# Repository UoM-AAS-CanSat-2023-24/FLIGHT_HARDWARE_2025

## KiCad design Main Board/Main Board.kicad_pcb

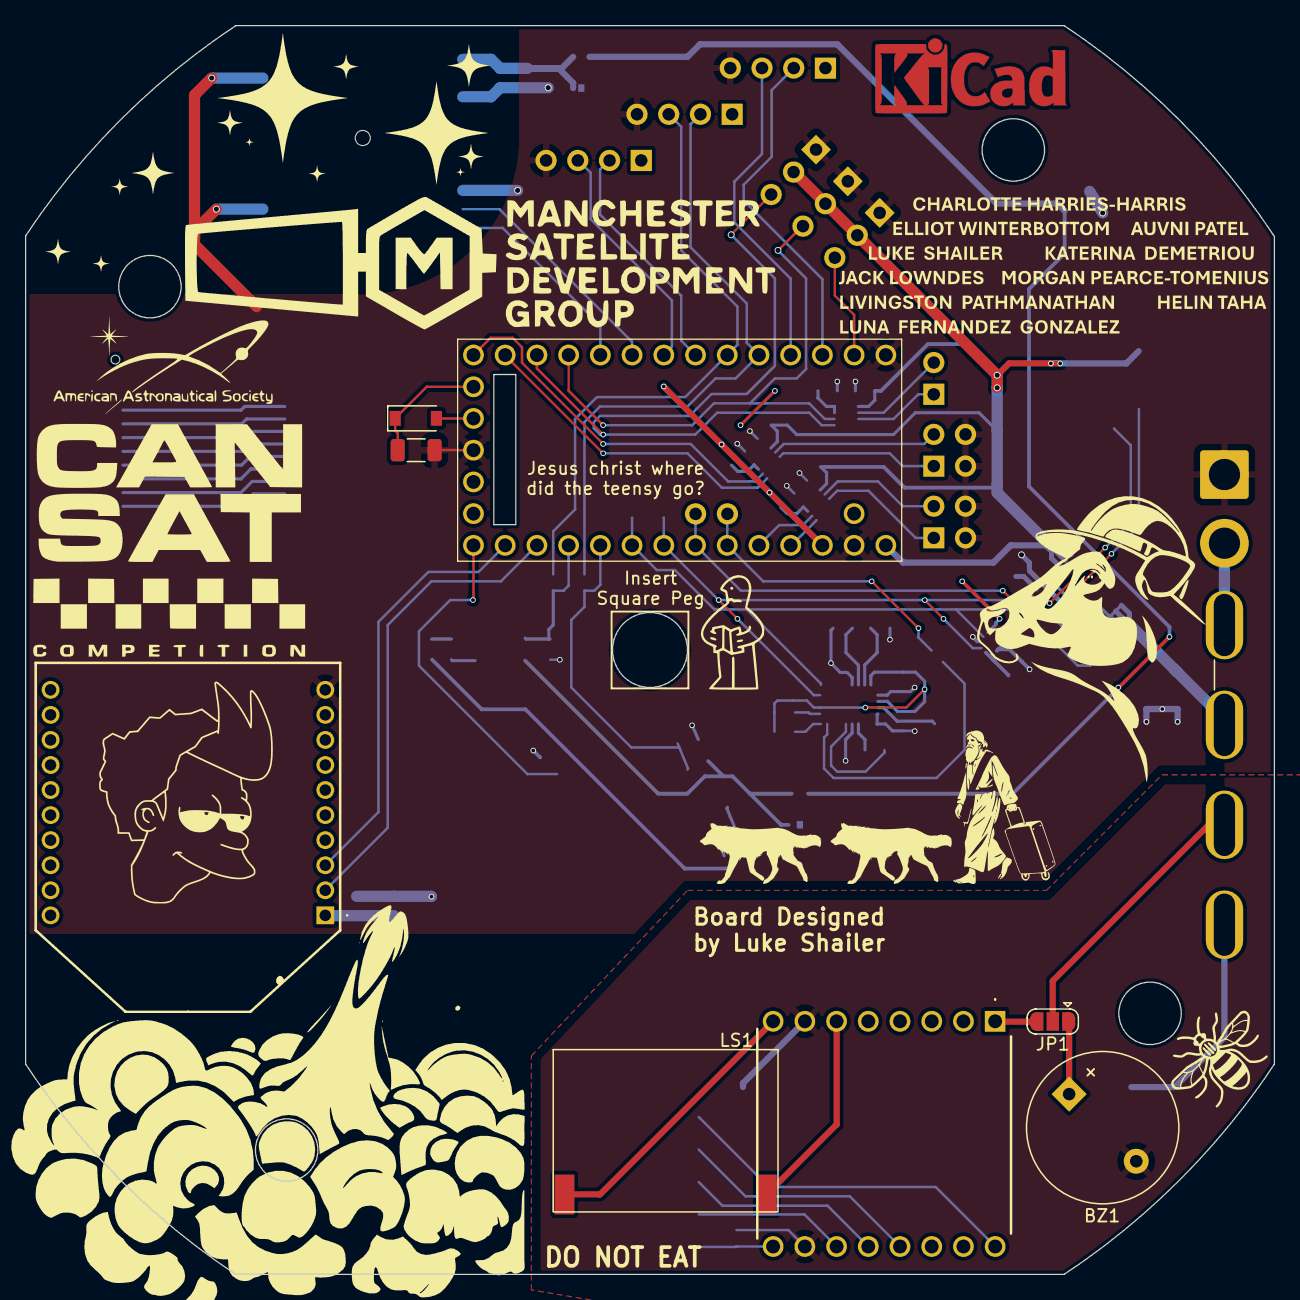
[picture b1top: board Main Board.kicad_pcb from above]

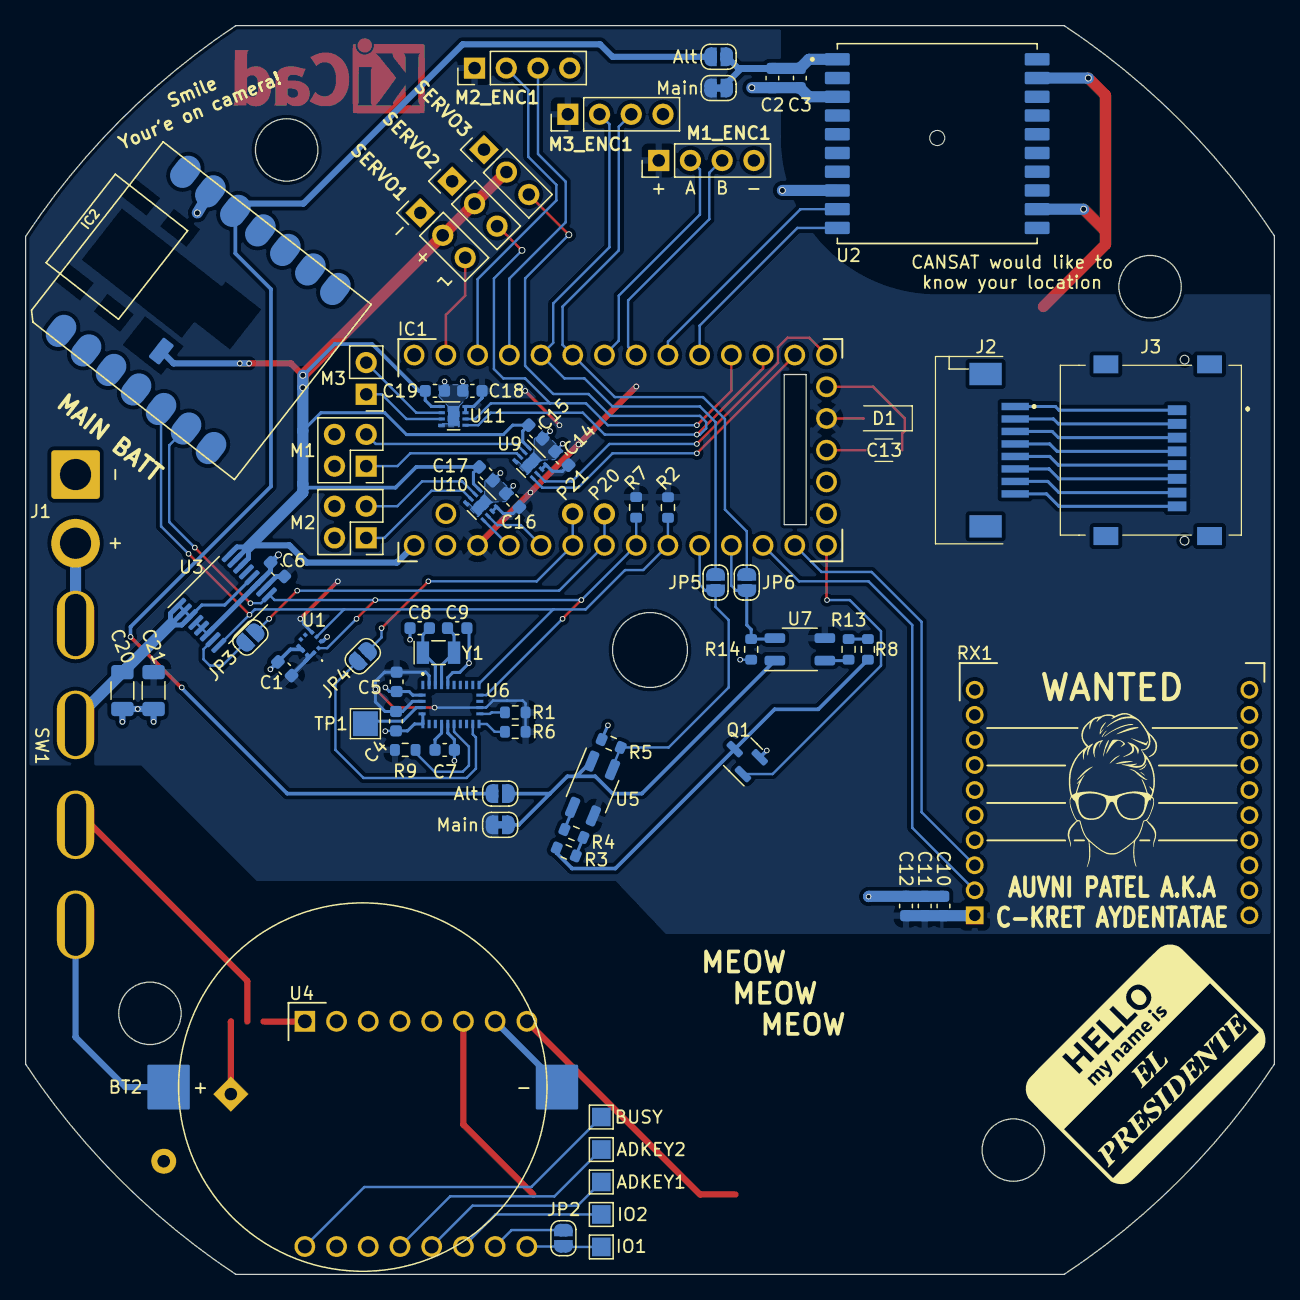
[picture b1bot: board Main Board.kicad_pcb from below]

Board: 2 copper layers, 100.0 x 100.0 mm, 82 parts (72 on the bottom side), 73 nets.

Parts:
BT2: CR2450 Battery Holder; 237-8264 Battery holder
BZ1: KXG1203C; Buzzer_12x9.5RM7.6
C1, C3, C4, C5, C6, C7, C14, C15, C16, C17, C18, C19: 0.1uF; C_0603_1608Metric
C2, C11: 1uF; C_0603_1608Metric
C8, C9, C10: 22pF; C_0603_1608Metric
C12: 10uF; C_0603_1608Metric
C13, C20, C21: 150uF; C_1206_3216Metric
D1: MBRX120LF; D_SOD-123
IC1: TEENSY_4.0; TEENSY40
IC2: MOUDLE-SEEEDUINO-XIAO-ESP32S3; MOUDLE14P-SMD-2.54-21X17.8MM
J1: MAIN BATT; SolderWire-2sqmm_1x02_P7.8mm_D2mm_OD3.9mm_Relief
J2: 68610814422
J3: 47219-2001; 472192001_wire_lock
J4: P20; PinHeader_1x01_P2.54mm_Vertical
J5: P21; PinHeader_1x01_P2.54mm_Vertical
JP1: SolderJumper_3_Open; SolderJumper-3_P1.3mm_Open_RoundedPad1.0x1.5mm
JP2, JP3, JP4, JP5, JP6: SolderJumper_2_Open; SolderJumper-2_P1.3mm_Open_RoundedPad1.0x1.5mm
JP7, JP9: Alt; SolderJumper-2_P1.3mm_Open_RoundedPad1.0x1.5mm
JP8, JP10: Main; SolderJumper-2_P1.3mm_Bridged_RoundedPad1.0x1.5mm
LS1: HDK-181308ZA-6P2; HDK-181308ZA-6P2 Speaker
M1: M1; PinHeader_2x02_P2.54mm_Vertical
M1_ENC1, M2_ENC1: M2_ENC; PinHeader_1x04_P2.54mm_Vertical
M2: M2; PinHeader_2x02_P2.54mm_Vertical
M3: M3; PinHeader_1x02_P2.54mm_Vertical
M3_ENC1: M1_ENC; PinHeader_1x04_P2.54mm_Vertical
Q1: DO2302E-Q; SOT-23
R1, R2, R6, R7, R9: 4K7; R_0603_1608Metric
R3, R4, R8, R13: 47R; R_0603_1608Metric
R5, R14: 6K65; R_0603_1608Metric
RX1: XB24CAWIT-001; XB24CAPIT001
SERVO1: Servo 2; PinHeader_1x03_P2.54mm_Vertical
SERVO2: Servo 1; PinHeader_1x03_P2.54mm_Vertical
SERVO3: Servo 3; PinHeader_1x03_P2.54mm_Vertical
SW1: Screw Switch; Board_Conn_CanSat
TP1: TestPoint; TestPoint_Pad_2.0x2.0mm
TP2: BUSY; TestPoint_Pad_1.5x1.5mm
TP3: ADKEY2; TestPoint_Pad_1.5x1.5mm
TP4: ADKEY1; TestPoint_Pad_1.5x1.5mm
TP5: IO2; TestPoint_Pad_1.5x1.5mm
TP6: IO1; TestPoint_Pad_1.5x1.5mm
U1: BMP581
U2: CD-PA1616D; PA1616D
U3: INA260; TSSOP-16_4.4x5mm_P0.65mm
U4: DFR0299
U5, U7: QRE1113GR; OnSemi_CASE100CY
U6: BNO085
U9, U10, U11: DRV8837; WSON-8-1EP_2x2mm_P0.5mm_EP0.9x1.6mm
Y1: CM7V-T1A 32.768KHZ 12.5PF ±20PPM TA QC; Crystal_SMD_MicroCrystal_CC7V-T1A-2Pin_3.2x1.5mm

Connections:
+3.3VP: IC2.12 (3V3), JP7.2 (B), JP9.2 (B)
+3V3: C1.1, C4.1, C5.1, C6.1, C10.1, C11.1, C12.1, C14.1, C16.1, C18.1, C21.1, D1.2 (A), IC1.16 (3.3V), IC1.31 (3.3V(250_MA_MAX)), JP8.2 (B), JP10.2 (B), M1_ENC1.1, M2_ENC1.1, M3_ENC1.1, R1.2, R2.2, R6.2, R7.2, R9.2, RX1.1 (VCC), U1.1 (VDDIO), U1.5 (SDO), U1.10 (VDD), U3.10 (VS), U5.3, U6.3 (VDD), U6.17 (SA0/H_MOSI_), U6.28 (VDDIO), U7.3, U9.7 (~SLEEP), U9.8 (VCC), U10.7 (~SLEEP), U10.8 (VCC), U11.7 (~SLEEP), U11.8 (VCC)
+BATT: C15.1, C17.1, C19.1, IC1.33 (VIN_(3.6_TO_5.5_VOLTS)), IC2.15 (VBATT), SERVO1.2, SERVO2.2, SERVO3.2, U3.14 (IN-), U3.15 (IN-), U3.16 (IN-), U9.1 (VM), U10.1 (VM), U11.1 (VM)
+BATT_high: C20.1, SW1.2, U3.1 (IN+), U3.2 (IN+), U3.3 (IN+), U3.12 (VBUS)
/Buzzer/Buzz_GND: BT2.2 (-), BZ1.2 (+), JP2.1 (A), U4.7 (GND_1), U4.10 (GND_2)
/CLK: J2.5, J3.5 (CLK)
/CMD: J2.3, J3.3 (CMD)
/D0: J2.7, J3.7 (DAT0)
/D1: J2.8, J3.8 (DAT1)
/D2: J2.1, J3.1 (DAT2)
/D3: J2.2, J3.2 (DAT3/CD)
/RTC_Battery: C13.1, D1.1 (K), IC1.15 (VBAT)
/VDD: J2.4, J3.4 (VDD)
/VSS: J2.6, J3.6 (VSS)
GND: C1.2, C2.2, C3.2, C4.2, C5.2, C6.2, C7.2, C8.2, C9.2, C10.2, C11.2, C12.2, C13.2, C14.2, C15.2, C16.2, C17.2, C18.2, C19.2, C20.2, C21.2, IC1.1 (GND_1), IC1.17 (GND_2), IC1.32 (GND_3), IC2.13 (GND), J1.1, M1.2, M1.4, M1_ENC1.4, M2.2, M2.4, M2_ENC1.4, M3_ENC1.4, Q1.2 (S), R5.1, R14.1, RX1.10 (GND), SERVO1.1, SERVO2.1, SERVO3.1, U1.3 (VSS_1), U1.8 (VSS_2), U1.9 (VSS_3), U2.3 (GND), U2.8 (GND), U2.12 (GND), U2.19 (GND), U3.4 (A1), U3.5 (A0), U3.6 (GND), U3.11 (GND), U6.2 (GND_1), U6.5 (PS1), U6.6 (PS0/WAKE), U6.10 (CLKSEL0), U6.25 (GND_2), U9.4 (GND), U9.9 (GND), U10.4 (GND), U10.9 (GND), U11.4 (GND), U11.9 (GND)
GPS_RX: IC1.10 (8), U2.10 (RX)
GPS_TX: IC1.9 (7), U2.9 (TX)
GYRO_RATE_A: IC1.24 (17), JP5.1 (A), R5.2, U5.4
GYRO_RATE_B: IC1.23 (16), JP6.1 (A), R14.2, U7.4
GYRO_RATE_EN: IC1.20 (13), Q1.1 (G)
IMU_INT: JP4.2 (B), U6.14 (H_INTN)
M1_ENC_A: IC1.7 (5), M1_ENC1.2
M1_ENC_B: IC1.8 (6), M1_ENC1.3
M1_IN1: IC1.29 (22), U10.6 (PH)
M1_IN2: IC1.30 (23), U10.5 (EN)
M2_ENC_A: IC1.3 (1), M2_ENC1.2
M2_ENC_B: IC1.4 (2), M2_ENC1.3
M2_IN1: IC1.14 (12), U9.6 (PH)
M2_IN2: IC1.13 (11), U9.5 (EN)
M3_ENC_A: IC1.5 (3), JP5.2 (B), M3_ENC1.2
M3_ENC_B: IC1.6 (4), JP6.2 (B), M3_ENC1.3
M3_IN1: IC1.11 (9), SERVO2.3, U11.6 (PH)
unnamed: BT2.1 (+), SW1.4 (2)
unnamed: BZ1.1 (-), JP1.1 (A)
unnamed: C7.1, U6.9 (CAP)
unnamed: C8.1, U6.27 (XIN32), Y1.1
unnamed: C9.1, U6.26 (XOUT32/CLKSEL1), Y1.2
unnamed: IC1.27 (20), J4.1, JP3.1 (A)
unnamed: IC1.28 (21), J5.1, JP4.1 (A)
unnamed: J1.2, SW1.1
unnamed: JP1.2 (C), SW1.3 (1)
unnamed: JP1.3 (B), U4.1 (VCC)
unnamed: LS1.1, U4.6 (SPK1)
unnamed: LS1.2, U4.8 (SPK2)
unnamed: M1.1, U9.3 (OUT2)
unnamed: M1.3, U9.2 (OUT1)
unnamed: M2.1, U10.3 (OUT2)
unnamed: M2.3, U10.2 (OUT1)
unnamed: M3.1, U11.3 (OUT2)
unnamed: M3.2, U11.2 (OUT1)
unnamed: Q1.3 (D), R3.1, R8.1
unnamed: R1.1, U6.16 (ENV_SDA)
unnamed: R3.2, R4.1
unnamed: R4.2, U5.2 (K)
unnamed: R6.1, U6.15 (ENV_SCL_)
unnamed: R8.2, R13.1
unnamed: R13.2, U7.2 (K)
unnamed: TP1.1, U6.4 (BOOTN)
unnamed: C2.1, C3.1, JP7.1 (A), JP8.1 (A), U2.1 (VCC)
unnamed: JP2.2 (B), TP6.1, U4.9 (IO1)
unnamed: TP5.1, U4.11 (IO2)
unnamed: TP4.1, U4.12 (ADKEY1)
unnamed: TP3.1, U4.13 (ADKEY2)
unnamed: TP2.1, U4.16 (BUSY)
unnamed: R9.1, U6.11 (NRST)
unnamed: JP9.1 (A), JP10.1 (A), U5.1 (A), U7.1 (A)
POWER_INT: JP3.2 (B), U3.7 (ALERT)
SCL0: IC1.26 (19), IC2.6 (PA9_A5_D5_SCL), R7.1, U1.2 (SCK), U3.9 (SCL), U6.19 (H_SCL/SCK/RX)
SDA0: IC1.25 (18), IC2.5 (PA8_A4_D4_SDA), R2.1, U1.4 (SDI), U3.8 (SDA), U6.20 (H_SDA/H_MISO/TX_)
SERVO_1: IC1.2 (0), SERVO1.3
SERVO_3: IC1.12 (10), SERVO3.3, U11.5 (EN)
XBEE_RX: IC1.21 (14), RX1.3 (DIN/~CONFIG)
XBEE_TX: IC1.22 (15), RX1.2 (DOUT)

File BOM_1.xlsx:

Ref | Qty / Board | Order Qty | Price | Cost / Board | Order Cost | Value | Description | Footprint | Vendor | Link | Minimum Order | Note
A1, A2, | 2 | 100 | 4.2999999999999997E-2 | 8.5999999999999993E-2 | 4.3 | M3 Lock Nut |  |  | RS | https://uk.rs-online.com/web/p/hex-nuts/2836760 | 100
A3, A4, | 2 | 100 | 0.02 | 0.04 | 2 | M3 Nut |  |  | RS | https://uk.rs-online.com/web/p/hex-nuts/2834295 | 100
A5, A6, | 2 | 100 | 2.7799999999999998E-2 | 5.6000000000000001E-2 | 2.78 | M3x10 |  |  | RS | https://uk.rs-online.com/web/p/machine-screws/3180575 | 100
BT2, | 1 | 3 | 1.49 | 1.49 | 4.47 | CR2450 Battery Holder | Single-cell battery | KiCad:237-8264 Battery holder | RS | https://uk.rs-online.com/web/p/battery-holders/2378264 | 1
BZ1, | 1 | 5 | 0.78700000000000003 | 0.78700000000000003 | 3.9350000000000001 | KXG1203C | Buzzer, polarized | Buzzer_Beeper:Buzzer_12x9.5RM7.6 | RS | https://uk.rs-online.com/web/p/piezo-buzzers/7716957 | 5
C1, C3, C4, C5, C6, C7, C14, C15, C16, C17, C18, C19, | 12 | 50 | 0.01 | 0.12 | 0.5 | 0.1uF | Unpolarized capacitor, small symbol | Capacitor_SMD:C_0603_1608Metric | RS | https://uk.rs-online.com/web/p/mlccs-multilayer-ceramic-capa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 | 25
C2, C11, | 2 | 100 | 7.0000000000000001E-3 | 1.4E-2 | 0.7 | 1uF | Unpolarized capacitor, small symbol | Capacitor_SMD:C_0603_1608Metric | RS | https://uk.rs-online.com/web/p/mlccs-multilayer-ceramic-capa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 | 100
C8, C9, C10, | 3 | 100 | 6.0000000000000001E-3 | 1.7999999999999999E-2 | 0.6 | 22pF | Unpolarized capacitor, small symbol | Capacitor_SMD:C_0603_1608Metric | RS | https://uk.rs-online.com/web/p/mlccs-multilayer-ceramic-capa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 | 100
C13, C20, C21, | 3 | 10 | 0.36699999999999999 | 1.101 | 3.67 | 150uF | Unpolarized capacitor, small symbol | Capacitor_SMD:C_1206_3216Metric | RS | https://uk.rs-online.com/web/p/mlccs-multilayer-ceramic-capa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 | 10
D1, | 1 | 3 | 0 | 0 | 0 | MBRX120LF | Schottky diode | Diode_SMD:D_SOD-123 | STOCK
D100, D101, | 2 | 6 | 0.2 | 0.4 | 1.2 | LED |  | LED_SMD:LED_0603_1608Metric | RS | https://uk.rs-online.com/web/p/leds/2790656 | 1 | NOTE Leds have a tendency of just dying so I would order 10 total for both boar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
IC1, | 1 | 3 | 30.37 | 30.37 | 91.11 | TEENSY_4.0 | Teensy USB Board, Version 4.0 | TEENSY:TEENSY40 | RS | https://uk.rs-online.com/web/p/microcontroller-development-t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
J3, | 1 | 3 | 1.47 | 1.47 | 4.41 | 47219-2001 | Micro SD Card Socket | SD card:472192001_wire_lock | RS | https://uk.rs-online.com/web/p/memory-card-connectors/8006845
MISC2, | 1 | 3 | 3.32 | 3.32 | 9.9600000000000009 | LIR2450 |  |  | RS | https://uk.rs-online.com/web/p/button-rechargeable-batteries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 | 1
Q1, | 1 | 3 | 0 | 0 | 0 | DO2302E-Q | N-MOSFET transistor, gate/source/drain | Package_TO_SOT_SMD:SOT-23 | STOCK
R1, R2, R6, R7, R9, | 5 | 50 | 8.0000000000000002E-3 | 0.04 | 0.4 | 4K7 | Resistor, small symbol | Resistor_SMD:R_0603_1608Metric | RS | https://uk.rs-online.com/web/p/surface-mount-resistors/7408877 | 50
R3, R4, R8, R13, | 4 | 50 | 3.0000000000000001E-3 | 1.2E-2 | 0.15 | 47R | Resistor, small symbol | Resistor_SMD:R_0603_1608Metric | RS | https://uk.rs-online.com/web/p/surface-mount-resistors/6316070 | 50
R5, R14, | 2 | 10 | 0.02 | 0.04 | 0.2 | 6K65 | Resistor, small symbol | Resistor_SMD:R_0603_1608Metric | RS | https://uk.rs-online.com/web/p/surface-mount-resistors/7087688 | 5
R100, R101, R102, | 3 | 100 | 1E-3 | 3.0000000000000001E-3 | 0.1 | 220R |  | Resistor_SMD:R_0603_1608Metric | RS | https://uk.rs-online.com/web/p/surface-mount-resistors/9013531 | 100
RX1, | 1 | 3 | 31.86 | 31.86 | 95.58 | XB24CAWIT-001 | Zigbee Modules - 802.15.4 XBee, S2C, 2.4GHz Through-hole,PCB ant | XBEE:XB24CAWIT001 | RS | https://uk.rs-online.com/web/p/communication-wireless-develo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
U1, | 1 | 3 | 2.75 | 2.75 | 8.25 | BMP581 | Pressure Sensor 4.35PSI ~ 18.13PSI (30kPa ~ 125kPa) Absolute 10-WFLGA | BMP581:BMP581 | Mouser | https://www.mouser.co.uk/ProductDetail/Bosch-Sensortec/BMP58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
U2, | 1 | 3 | 19.95 | 19.95 | 59.85 | CD-PA1616D |  | KiCad:PA1616D | Adafruit | https://www.adafruit.com/product/5186
U3, | 1 | 3 | 3.1259999999999999 | 3.1259999999999999 | 9.3780000000000001 | INA260 | Current/power/voltage monitor with Integrated 2mÃŽÂ© Shunt Resistor, 2.7V - 5.5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 | Package_SO:TSSOP-16_4.4x5mm_P0.65mm | RS | https://uk.rs-online.com/web/p/current-sensing-amplifiers/20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
U5, U7, | 2 | 10 | 0.97699999999999998 | 1.954 | 9.77 | QRE1113GR | Miniature Reflective Optical Object Sensor, SMD-4 | OptoDevice:OnSemi_CASE100CY | RS | https://uk.rs-online.com/web/p/reflective-optical-sensors/7613984 | 5
U6, | 1 | 3 | 12.77 | 12.77 | 38.31 | BNO085 | Board Mount Motion & Position Sensors 9-axis IMU | BNO056:BNO085 | Mouser | https://www.mouser.co.uk/ProductDetail/CEVA/BNO085?qs=ulEaXI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
U8, | 1 | 3 | 11.06 | 11.06 | 33.18 | MOUDLE-SEEEDUINO-XIAO-ESP32S3 |  | sense:MOUDLE14P-SMD-2.54-21X17.8MM | Mouser | https://www.mouser.co.uk/ProductDetail/Seeed-Studio/11399111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 | 1
U9, U10, U11, | 3 | 10 | 0.371 | 1.113 | 3.71 | DRV8837 | H-Bridge driver, 1.8A, Low Voltage, PH/EN input, WSON-8 | Package_SON:WSON-8-1EP_2x2mm_P0.5mm_EP0.9x1.6mm | RS | https://uk.rs-online.com/web/p/motor-driver-ics/2264762 | 10
Y1, | 1 | 5 | 0.79400000000000004 | 0.79400000000000004 | 3.97 | CM7V-T1A 32.768KHZ 12.5PF Ã‚Â±20PPM TA QC | Two pin crystal, small symbol | Crystal:Crystal_SMD_MicroCrystal_CC7V-T1A-2Pin_3.2x1.5mm | RS | https://uk.rs-online.com/web/p/crystal-units/7293271 | 5

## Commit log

2025-07-16 Add files via upload
    Add Main PCB kicad + gerber files. STEPs too large to add
2025-07-16 Add screw switch files via upload
    Add kicad, gerber, and step files for screw switch PCB
